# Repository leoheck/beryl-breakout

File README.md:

Beryl Breakout Board

Simple, breakout for the huge IC made in the past.
This is still a work in progress.

> This project uses Kicad 5.6.1

[Beryl MBLite Soc](https://corfu.pucrs.br/svn/mblite-chip/) was finished in March 2014 and can be accessed through GAPH's old SVN.

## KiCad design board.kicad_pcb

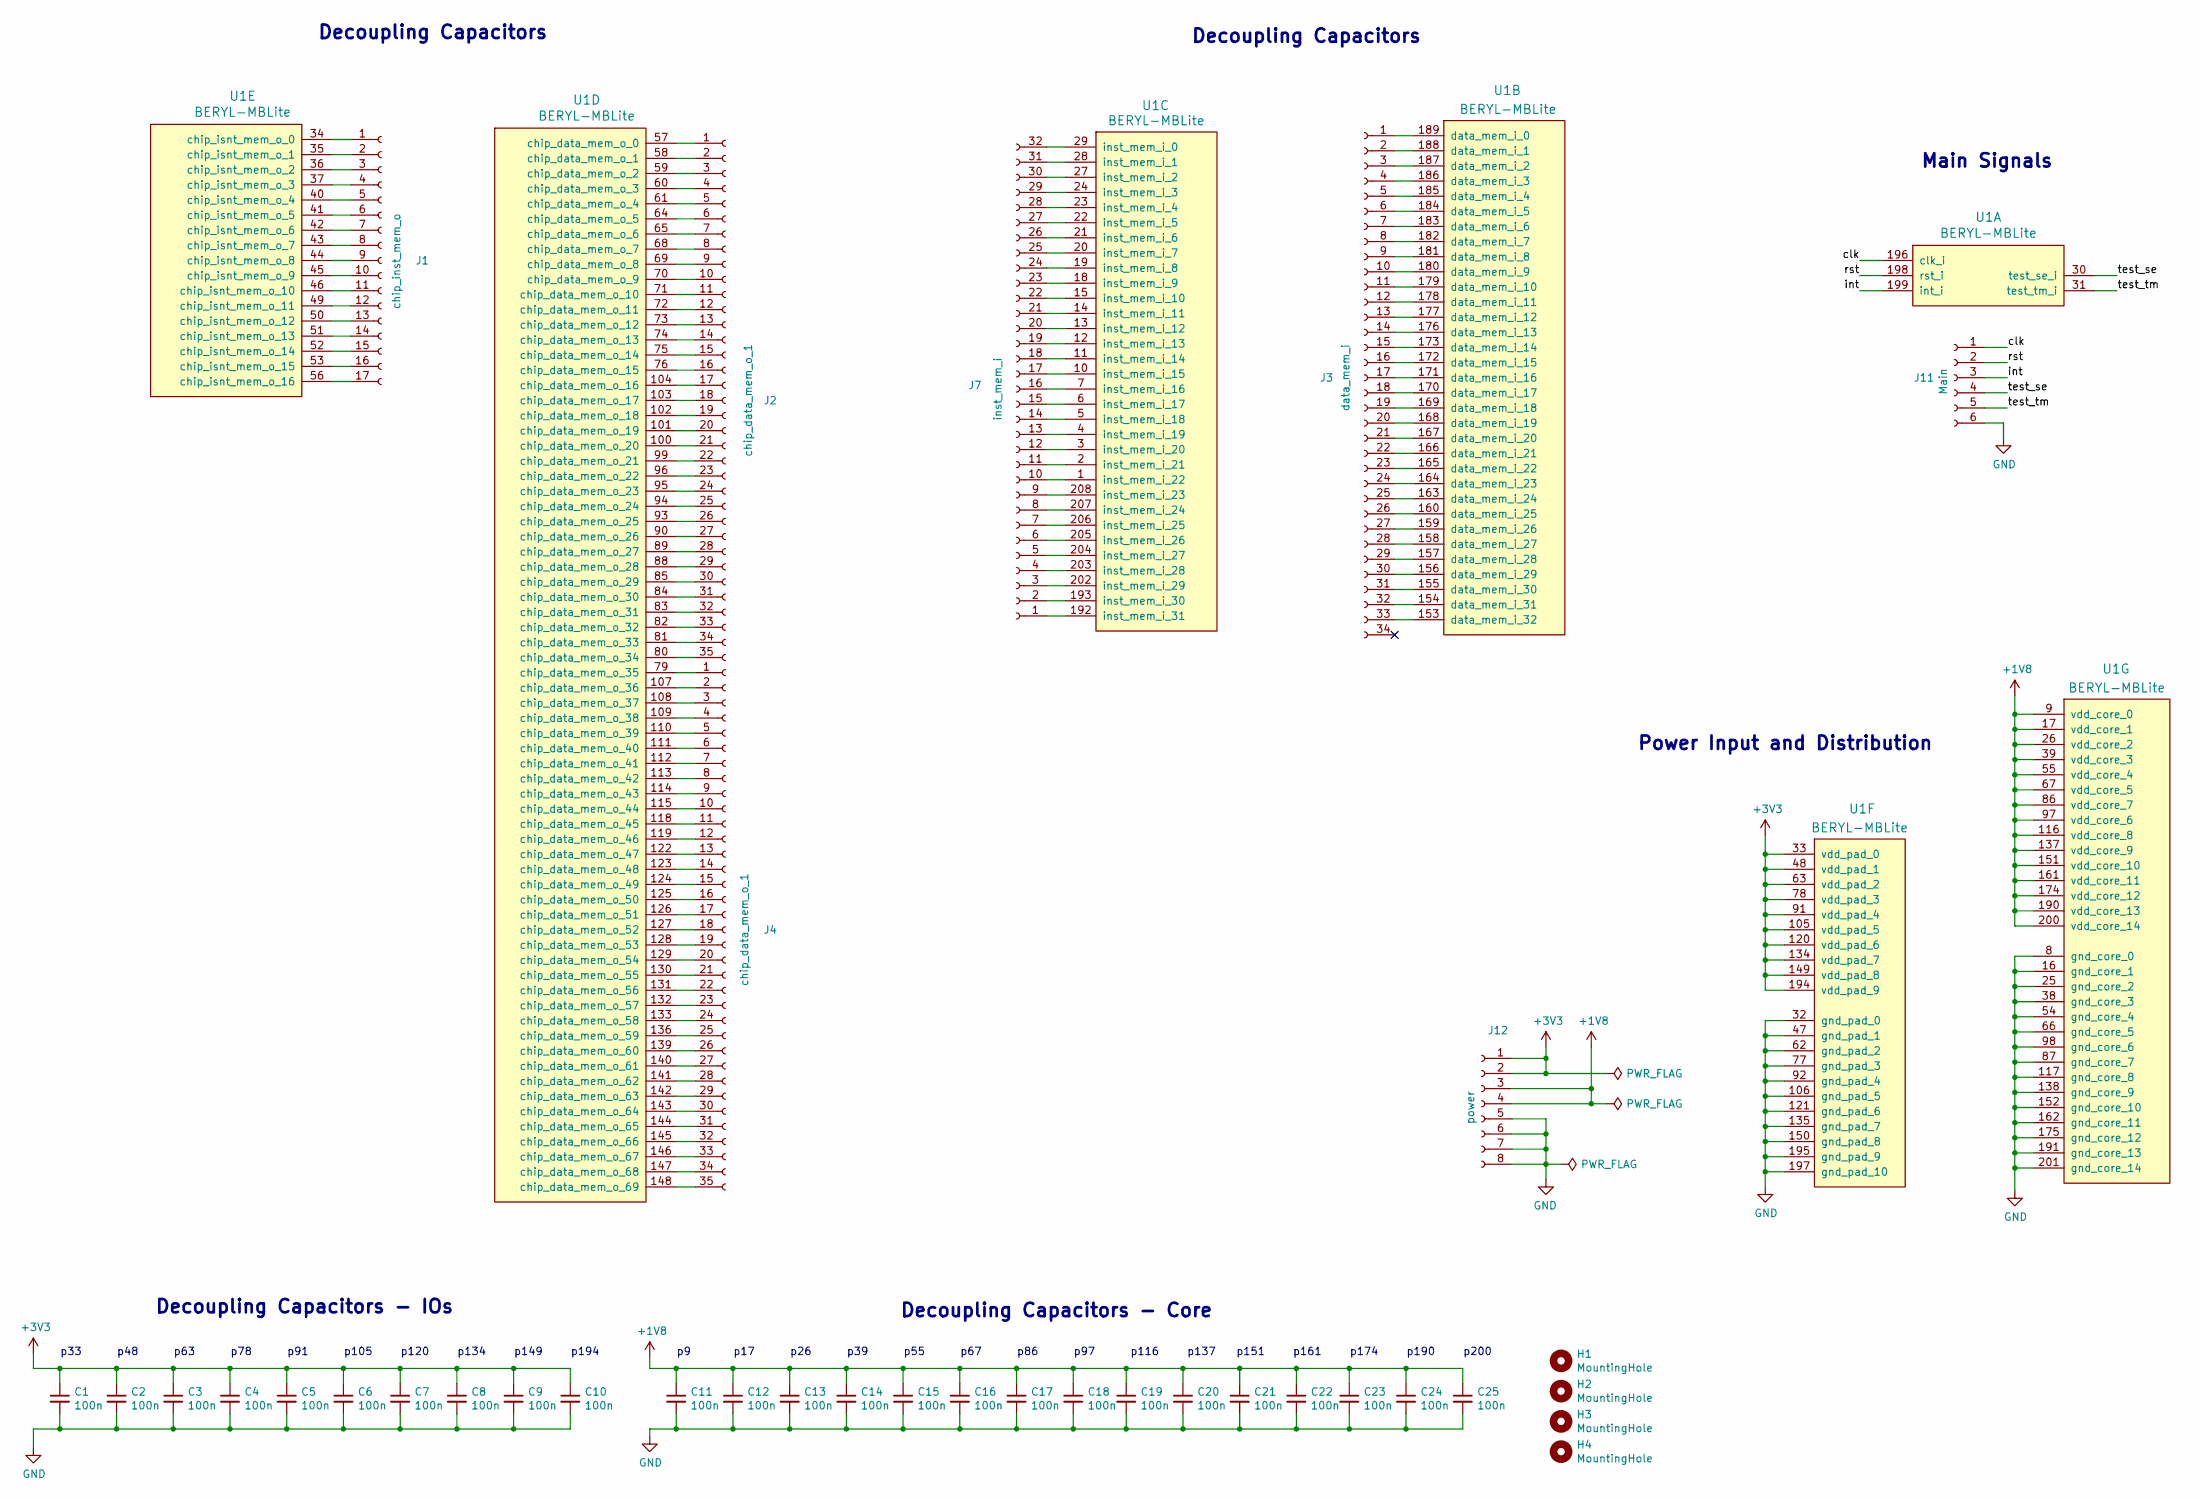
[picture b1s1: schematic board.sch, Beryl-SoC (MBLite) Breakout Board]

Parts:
C1, C2, C3, C4, C5, C6, C7, C8, C9, C10, C11, C12, C13, C14, C15, C16, C17, C18, C19, C20, C21, C22, C23, C24, C25: 100n; C_0805_2012Metric_Pad1.15x1.40mm_HandSolder
H1, H2, H3, H4: MountingHole; MountingHole_2.5mm
J1: chip_inst_mem_o; PinSocket_2x09_P2.54mm_Vertical_SMD
J2, J4: chip_data_mem_o_1; PinSocket_2x18_P2.54mm_Vertical_SMD
J3: data_mem_i; PinSocket_2x17_P2.54mm_Vertical_SMD
J7: inst_mem_i; PinSocket_2x16_P2.54mm_Vertical_SMD
J11: Main; PinSocket_2x03_P2.54mm_Vertical_SMD
J12: power; PinSocket_2x04_P2.54mm_Vertical_SMD
U1: BERYL-MBLite; PGA-290_17x17_43.18x43.18mm

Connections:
+1V8: C11.1, C12.1, C13.1, C14.1, C15.1, C16.1, C17.1, C18.1, C19.1, C20.1, C21.1, C22.1, C23.1, C24.1, C25.1, J12.3, J12.4, U1.9 (vdd_core_0), U1.17 (vdd_core_1), U1.26 (vdd_core_2), U1.39 (vdd_core_3), U1.55 (vdd_core_4), U1.67 (vdd_core_5), U1.86 (vdd_core_7), U1.97 (vdd_core_6), U1.116 (vdd_core_8), U1.137 (vdd_core_9), U1.151 (vdd_core_10), U1.161 (vdd_core_11), U1.174 (vdd_core_12), U1.190 (vdd_core_13), U1.200 (vdd_core_14)
+3V3: C1.1, C2.1, C3.1, C4.1, C5.1, C6.1, C7.1, C8.1, C9.1, C10.1, J12.1, J12.2, U1.33 (vdd_pad_0), U1.48 (vdd_pad_1), U1.63 (vdd_pad_2), U1.78 (vdd_pad_3), U1.91 (vdd_pad_4), U1.105 (vdd_pad_5), U1.120 (vdd_pad_6), U1.134 (vdd_pad_7), U1.149 (vdd_pad_8), U1.194 (vdd_pad_9)
/clk: J11.1, U1.196 (clk_i)
/int: J11.3, U1.199 (int_i)
/rst: J11.2, U1.198 (rst_i)
/test_se: J11.4, U1.30 (test_se_i)
/test_tm: J11.5, U1.31 (test_tm_i)
GND: C1.2, C2.2, C3.2, C4.2, C5.2, C6.2, C7.2, C8.2, C9.2, C10.2, C11.2, C12.2, C13.2, C14.2, C15.2, C16.2, C17.2, C18.2, C19.2, C20.2, C21.2, C22.2, C23.2, C24.2, C25.2, J11.6, J12.5, J12.6, J12.7, J12.8, U1.8 (gnd_core_0), U1.16 (gnd_core_1), U1.25 (gnd_core_2), U1.32 (gnd_pad_0), U1.38 (gnd_core_3), U1.47 (gnd_pad_1), U1.54 (gnd_core_4), U1.62 (gnd_pad_2), U1.66 (gnd_core_5), U1.77 (gnd_pad_3), U1.87 (gnd_core_7), U1.92 (gnd_pad_4), U1.98 (gnd_core_6), U1.106 (gnd_pad_5), U1.117 (gnd_core_8), U1.121 (gnd_pad_6), U1.135 (gnd_pad_7), U1.138 (gnd_core_9), U1.150 (gnd_pad_8), U1.152 (gnd_core_10), U1.162 (gnd_core_11), U1.175 (gnd_core_12), U1.191 (gnd_core_13), U1.195 (gnd_pad_9), U1.197 (gnd_pad_10), U1.201 (gnd_core_14)
unnamed: J1.1, U1.34 (chip_isnt_mem_o_0)
unnamed: J1.2, U1.35 (chip_isnt_mem_o_1)
unnamed: J1.3, U1.36 (chip_isnt_mem_o_2)
unnamed: J1.4, U1.37 (chip_isnt_mem_o_3)
unnamed: J1.5, U1.40 (chip_isnt_mem_o_4)
unnamed: J1.6, U1.41 (chip_isnt_mem_o_5)
unnamed: J1.7, U1.42 (chip_isnt_mem_o_6)
unnamed: J1.8, U1.43 (chip_isnt_mem_o_7)
unnamed: J1.9, U1.44 (chip_isnt_mem_o_8)
unnamed: J1.10, U1.45 (chip_isnt_mem_o_9)
unnamed: J1.11, U1.46 (chip_isnt_mem_o_10)
unnamed: J1.12, U1.49 (chip_isnt_mem_o_11)
unnamed: J1.13, U1.50 (chip_isnt_mem_o_12)
unnamed: J1.14, U1.51 (chip_isnt_mem_o_13)
unnamed: J1.15, U1.52 (chip_isnt_mem_o_14)
unnamed: J1.16, U1.53 (chip_isnt_mem_o_15)
unnamed: J1.17, U1.56 (chip_isnt_mem_o_16)
unnamed: J2.1, U1.57 (chip_data_mem_o_0)
unnamed: J2.2, U1.58 (chip_data_mem_o_1)
unnamed: J2.3, U1.59 (chip_data_mem_o_2)
unnamed: J2.4, U1.60 (chip_data_mem_o_3)
unnamed: J2.5, U1.61 (chip_data_mem_o_4)
unnamed: J2.6, U1.64 (chip_data_mem_o_5)
unnamed: J2.7, U1.65 (chip_data_mem_o_6)
unnamed: J2.8, U1.68 (chip_data_mem_o_7)
unnamed: J2.9, U1.69 (chip_data_mem_o_8)
unnamed: J2.10, U1.70 (chip_data_mem_o_9)
unnamed: J2.11, U1.71 (chip_data_mem_o_10)
unnamed: J2.12, U1.72 (chip_data_mem_o_11)
unnamed: J2.13, U1.73 (chip_data_mem_o_12)
unnamed: J2.14, U1.74 (chip_data_mem_o_13)
unnamed: J2.15, U1.75 (chip_data_mem_o_14)
unnamed: J2.16, U1.76 (chip_data_mem_o_15)
unnamed: J2.17, U1.104 (chip_data_mem_o_16)
unnamed: J2.18, U1.103 (chip_data_mem_o_17)
unnamed: J2.19, U1.102 (chip_data_mem_o_18)
unnamed: J2.20, U1.101 (chip_data_mem_o_19)
unnamed: J2.21, U1.100 (chip_data_mem_o_20)
unnamed: J2.22, U1.99 (chip_data_mem_o_21)
unnamed: J2.23, U1.96 (chip_data_mem_o_22)
unnamed: J2.24, U1.95 (chip_data_mem_o_23)
unnamed: J2.25, U1.94 (chip_data_mem_o_24)
unnamed: J2.26, U1.93 (chip_data_mem_o_25)
unnamed: J2.27, U1.90 (chip_data_mem_o_26)
unnamed: J2.28, U1.89 (chip_data_mem_o_27)
unnamed: J2.29, U1.88 (chip_data_mem_o_28)
unnamed: J2.30, U1.85 (chip_data_mem_o_29)
unnamed: J2.31, U1.84 (chip_data_mem_o_30)
unnamed: J2.32, U1.83 (chip_data_mem_o_31)
unnamed: J2.33, U1.82 (chip_data_mem_o_32)
unnamed: J2.34, U1.81 (chip_data_mem_o_33)
unnamed: J2.35, U1.80 (chip_data_mem_o_34)
unnamed: J3.1, U1.189 (data_mem_i_0)
unnamed: J3.2, U1.188 (data_mem_i_1)
unnamed: J3.3, U1.187 (data_mem_i_2)
unnamed: J3.4, U1.186 (data_mem_i_3)
unnamed: J3.5, U1.185 (data_mem_i_4)
unnamed: J3.6, U1.184 (data_mem_i_5)
unnamed: J3.7, U1.183 (data_mem_i_6)
unnamed: J3.8, U1.182 (data_mem_i_7)
unnamed: J3.9, U1.181 (data_mem_i_8)
unnamed: J3.10, U1.180 (data_mem_i_9)
unnamed: J3.11, U1.179 (data_mem_i_10)
unnamed: J3.12, U1.178 (data_mem_i_11)
unnamed: J3.13, U1.177 (data_mem_i_12)
unnamed: J3.14, U1.176 (data_mem_i_13)
unnamed: J3.15, U1.173 (data_mem_i_14)
unnamed: J3.16, U1.172 (data_mem_i_15)
unnamed: J3.17, U1.171 (data_mem_i_16)
unnamed: J3.18, U1.170 (data_mem_i_17)
unnamed: J3.19, U1.169 (data_mem_i_18)
unnamed: J3.20, U1.168 (data_mem_i_19)
unnamed: J3.21, U1.167 (data_mem_i_20)
unnamed: J3.22, U1.166 (data_mem_i_21)
unnamed: J3.23, U1.165 (data_mem_i_22)
unnamed: J3.24, U1.164 (data_mem_i_23)
unnamed: J3.25, U1.163 (data_mem_i_24)
unnamed: J3.26, U1.160 (data_mem_i_25)
unnamed: J3.27, U1.159 (data_mem_i_26)
unnamed: J3.28, U1.158 (data_mem_i_27)
unnamed: J3.29, U1.157 (data_mem_i_28)
unnamed: J3.30, U1.156 (data_mem_i_29)
unnamed: J3.31, U1.155 (data_mem_i_30)
unnamed: J3.32, U1.154 (data_mem_i_31)
unnamed: J3.33, U1.153 (data_mem_i_32)
unnamed: J4.1, U1.79 (chip_data_mem_o_35)
unnamed: J4.2, U1.107 (chip_data_mem_o_36)
unnamed: J4.3, U1.108 (chip_data_mem_o_37)
unnamed: J4.4, U1.109 (chip_data_mem_o_38)
unnamed: J4.5, U1.110 (chip_data_mem_o_39)
unnamed: J4.6, U1.111 (chip_data_mem_o_40)
unnamed: J4.7, U1.112 (chip_data_mem_o_41)
unnamed: J4.8, U1.113 (chip_data_mem_o_42)
unnamed: J4.9, U1.114 (chip_data_mem_o_43)
unnamed: J4.10, U1.115 (chip_data_mem_o_44)
unnamed: J4.11, U1.118 (chip_data_mem_o_45)
unnamed: J4.12, U1.119 (chip_data_mem_o_46)
unnamed: J4.13, U1.122 (chip_data_mem_o_47)
unnamed: J4.14, U1.123 (chip_data_mem_o_48)
unnamed: J4.15, U1.124 (chip_data_mem_o_49)
unnamed: J4.16, U1.125 (chip_data_mem_o_50)
unnamed: J4.17, U1.126 (chip_data_mem_o_51)
unnamed: J4.18, U1.127 (chip_data_mem_o_52)
unnamed: J4.19, U1.128 (chip_data_mem_o_53)
unnamed: J4.20, U1.129 (chip_data_mem_o_54)
unnamed: J4.21, U1.130 (chip_data_mem_o_55)
unnamed: J4.22, U1.131 (chip_data_mem_o_56)
unnamed: J4.23, U1.132 (chip_data_mem_o_57)
unnamed: J4.24, U1.133 (chip_data_mem_o_58)
unnamed: J4.25, U1.136 (chip_data_mem_o_59)
unnamed: J4.26, U1.139 (chip_data_mem_o_60)
unnamed: J4.27, U1.140 (chip_data_mem_o_61)
unnamed: J4.28, U1.141 (chip_data_mem_o_62)
unnamed: J4.29, U1.142 (chip_data_mem_o_63)
unnamed: J4.30, U1.143 (chip_data_mem_o_64)
unnamed: J4.31, U1.144 (chip_data_mem_o_65)
unnamed: J4.32, U1.145 (chip_data_mem_o_66)
unnamed: J4.33, U1.146 (chip_data_mem_o_67)
unnamed: J4.34, U1.147 (chip_data_mem_o_68)
unnamed: J4.35, U1.148 (chip_data_mem_o_69)
unnamed: J7.1, U1.192 (inst_mem_i_31)
unnamed: J7.2, U1.193 (inst_mem_i_30)
unnamed: J7.3, U1.202 (inst_mem_i_29)
unnamed: J7.4, U1.203 (inst_mem_i_28)
unnamed: J7.5, U1.204 (inst_mem_i_27)
unnamed: J7.6, U1.205 (inst_mem_i_26)
unnamed: J7.7, U1.206 (inst_mem_i_25)
unnamed: J7.8, U1.207 (inst_mem_i_24)
unnamed: J7.9, U1.208 (inst_mem_i_23)
unnamed: J7.10, U1.1 (inst_mem_i_22)
unnamed: J7.11, U1.2 (inst_mem_i_21)
unnamed: J7.12, U1.3 (inst_mem_i_20)
unnamed: J7.13, U1.4 (inst_mem_i_19)
unnamed: J7.14, U1.5 (inst_mem_i_18)
unnamed: J7.15, U1.6 (inst_mem_i_17)
unnamed: J7.16, U1.7 (inst_mem_i_16)
unnamed: J7.17, U1.10 (inst_mem_i_15)
unnamed: J7.18, U1.11 (inst_mem_i_14)
unnamed: J7.19, U1.12 (inst_mem_i_13)
unnamed: J7.20, U1.13 (inst_mem_i_12)
unnamed: J7.21, U1.14 (inst_mem_i_11)
unnamed: J7.22, U1.15 (inst_mem_i_10)
unnamed: J7.23, U1.18 (inst_mem_i_9)
unnamed: J7.24, U1.19 (inst_mem_i_8)
unnamed: J7.25, U1.20 (inst_mem_i_7)
unnamed: J7.26, U1.21 (inst_mem_i_6)
unnamed: J7.27, U1.22 (inst_mem_i_5)
unnamed: J7.28, U1.23 (inst_mem_i_4)
unnamed: J7.29, U1.24 (inst_mem_i_3)
unnamed: J7.30, U1.27 (inst_mem_i_2)
unnamed: J7.31, U1.28 (inst_mem_i_1)
unnamed: J7.32, U1.29 (inst_mem_i_0)

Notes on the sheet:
Decoupling Capacitors - IOs
Power Input and Distribution
Main Signals
Decoupling Capacitors
p33
p48
p78
p105
p120
p134
p63
p149
p91
p194
Decoupling Capacitors - Core
p17
p39
p67
p86
p26
p55
p137
p116
p97
p151
p161
p200
p190
p174

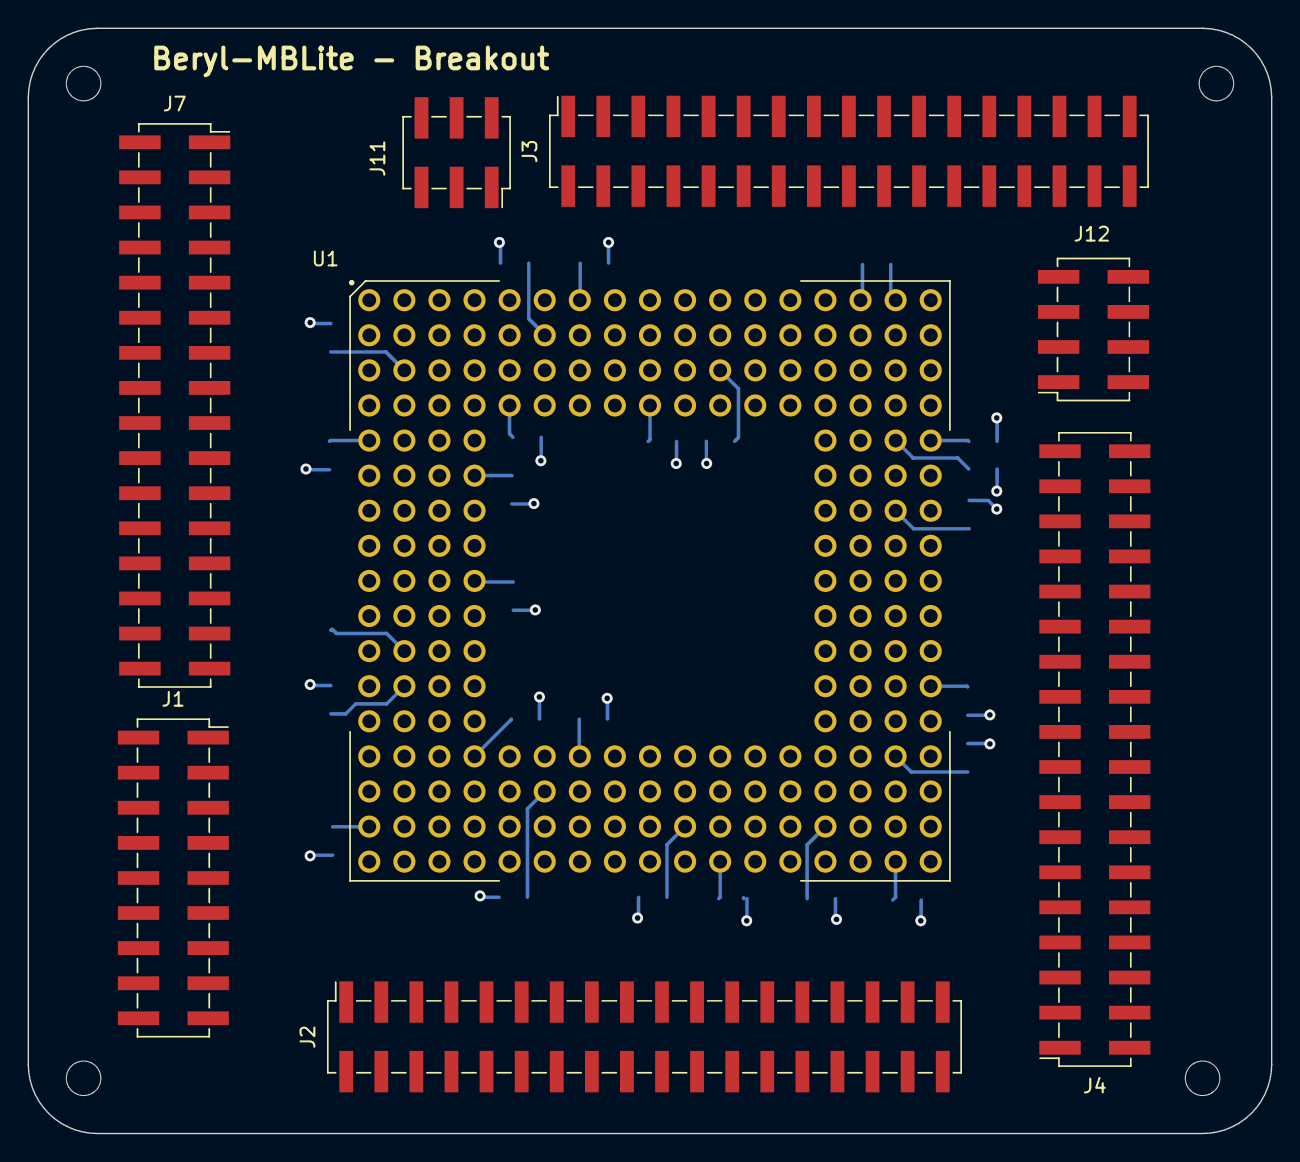
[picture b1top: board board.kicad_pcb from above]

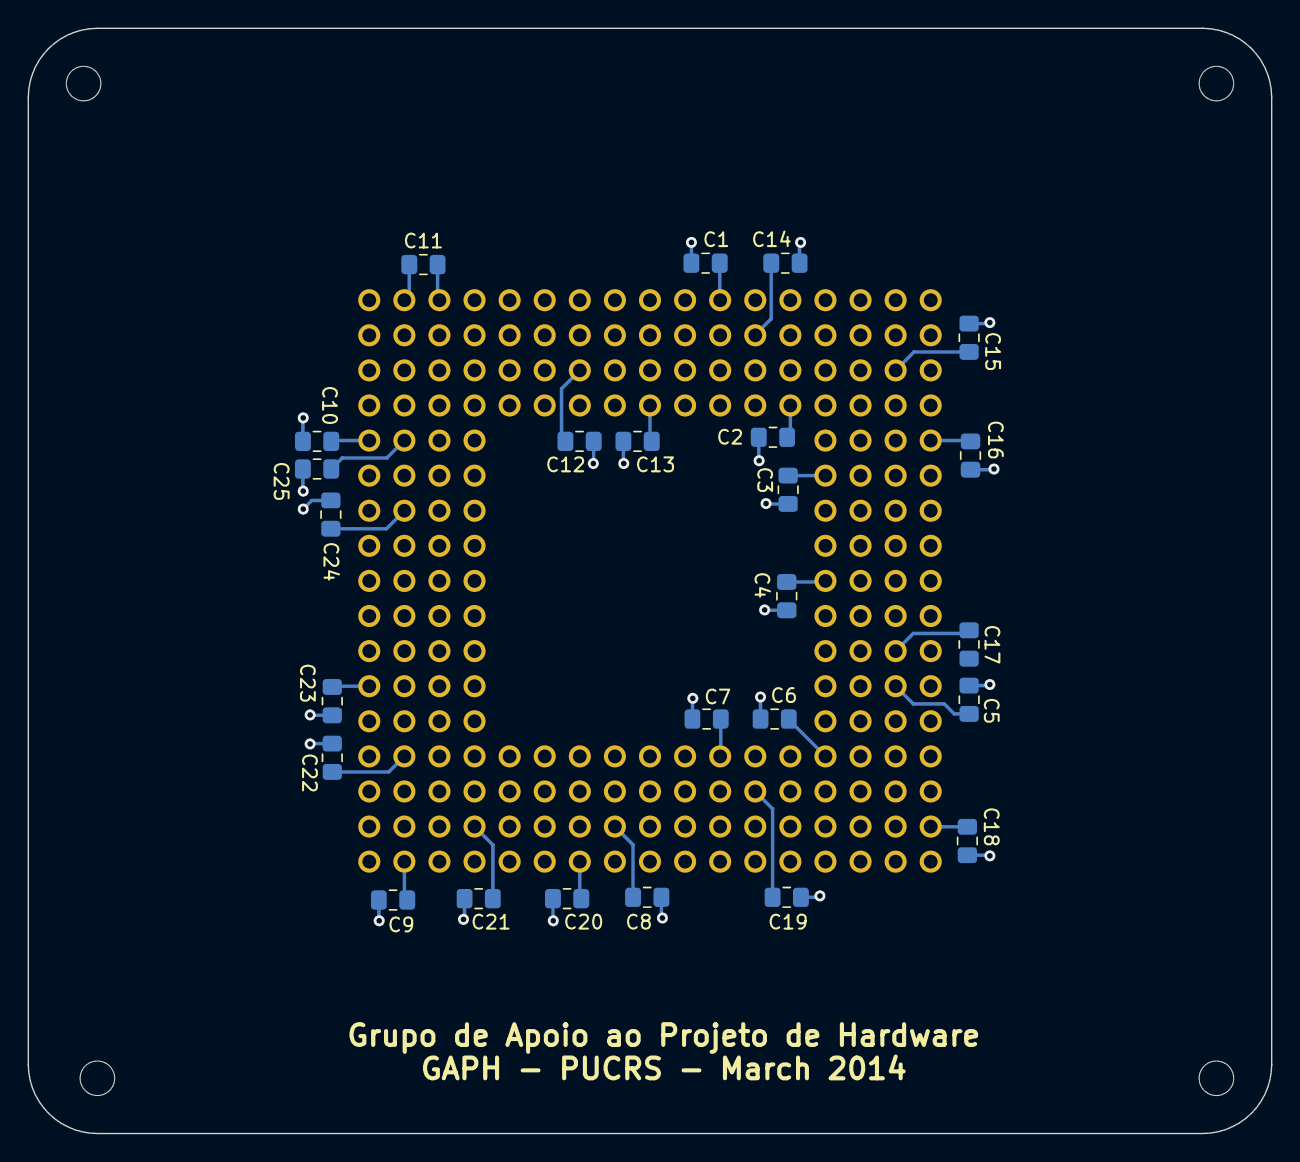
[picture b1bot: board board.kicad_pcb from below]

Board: 4 copper layers, 90.0 x 80.0 mm, 37 parts (25 on the bottom side), 160 nets.

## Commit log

2021-01-24 Add library submodule
2021-01-24 Update library submodule
2021-01-24 Initial files
2021-01-24 Change headers to SMD and add decoupling capacitors
2021-01-24 Improve capacitors placement
2021-01-24 Update images
2021-01-24 Update info
